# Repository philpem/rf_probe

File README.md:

# High impedance RF probes #

This repository contains a bunch of designs based on the Elektor "Poor Man's 1-GHz Active Probe":

* Elektor 1GHz RF Probe.brd - the original PCB design on which the others are based.
* Buffered 1GHz RF Probe.brd - the Elektor design, modified by myself to add an MAR-6 buffer to try and remove the -20dB probe attenuation.
* Buffered 1GHz RF Probe SMA.brd - same as above, but with an SMA connector for the RF output.

Refer to the Elektor article "Poor Man's 1-GHz Active Probe" in the October 2004 issue of Elektor for more information.

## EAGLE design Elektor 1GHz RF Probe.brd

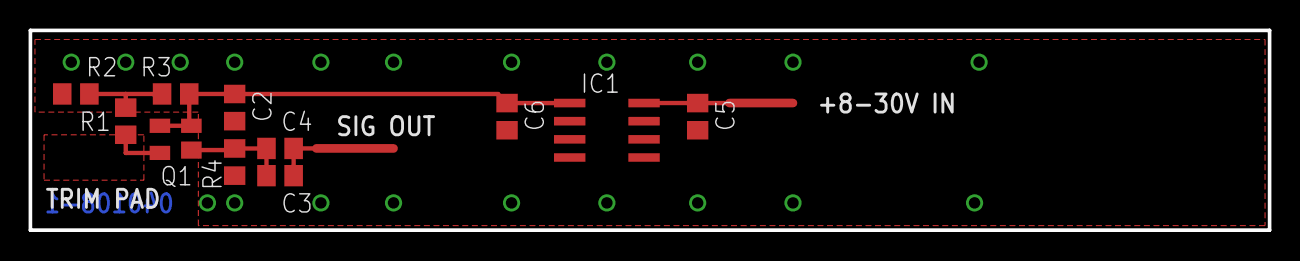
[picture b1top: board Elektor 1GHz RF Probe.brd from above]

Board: 2 copper layers, 86.7 x 14.0 mm, 11 parts (0 on the bottom side), 7 nets.

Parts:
C2: 1n; C0805
C3, C4: C0805
C5, C6: 470n; C0805
IC1: 78L05SMD; SO08
Q1: BF998; SOT143
R1: 10M; R0805
R2: 4k7; R0805
R3: 6k8; R0805
R4: 47R; R0805

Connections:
+5B: C2.1, C6.1, IC1.1, Q1.2, Q1.3, R3.1
GND: C2.2, C5.2, C6.2, IC1.2, IC1.3, IC1.6, IC1.7, R2.1, R4.2
unnamed: C3.1, C4.1, Q1.1, R4.1
unnamed: R1.2, R2.2, R3.2
unnamed: C5.1, IC1.8
SIGNAL_IN: Q1.4, R1.1
SIGNAL_OUT: C3.2, C4.2

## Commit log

2014-11-23 Add board outline, fix mirroring of "040108-1" text on bottom layer
2014-11-23 Make board dimension outline lines a bit thinner
2014-11-23 README.md edited online with Bitbucket
